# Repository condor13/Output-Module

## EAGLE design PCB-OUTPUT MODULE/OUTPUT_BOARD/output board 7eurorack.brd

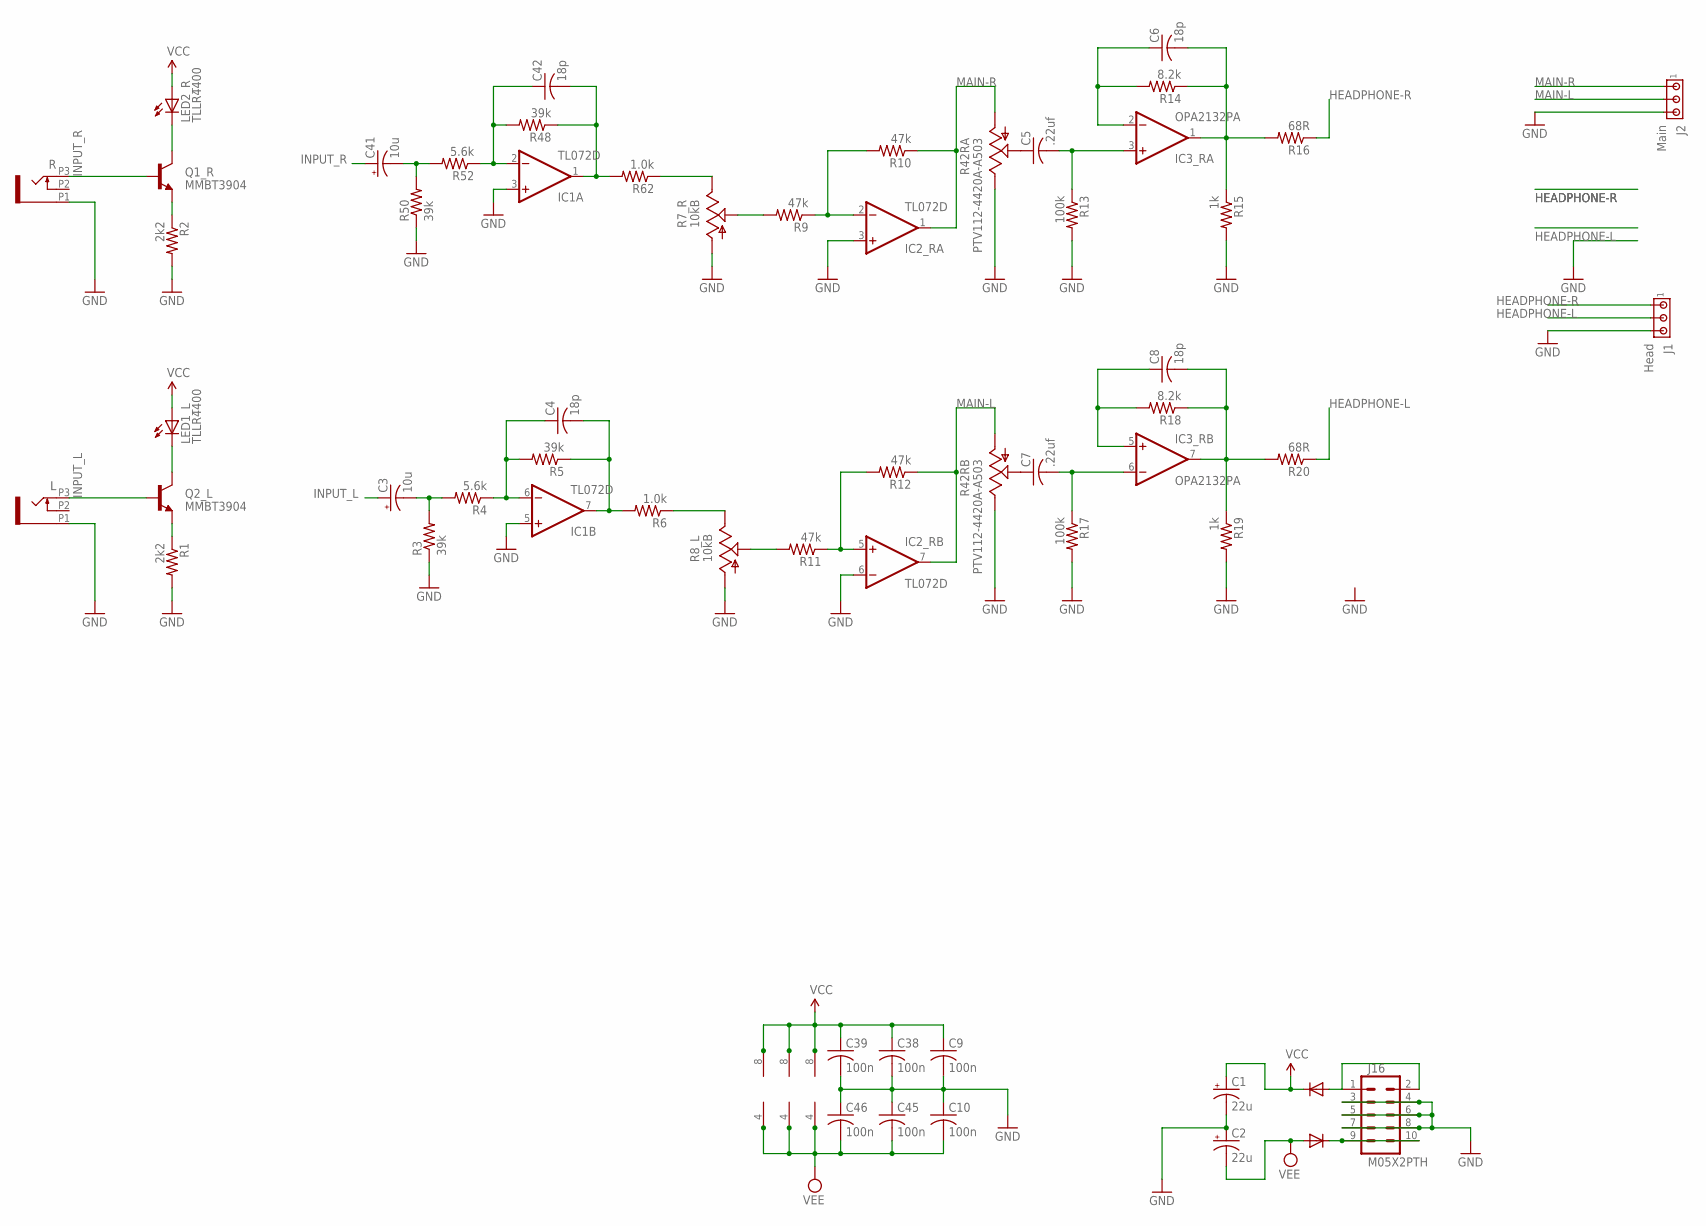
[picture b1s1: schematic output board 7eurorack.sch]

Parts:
C1, C2: 22u; PANASONIC_B
C3, C41: 10u; PANASONIC_B
C4, C6, C8, C42: 18p; C0603
C5, C7: .22uf; C0603
C9, C10, C38, C39, C45, C46: 100n; C0603
D1, D2: 1N5819HW; SOD123
IC1, IC2_R: TL072D; SO08
IC3_R: OPA2132PA; SO08
J1: Head; 10X03MTA
J2: Main; 10X03MTA
J16: M05X2PTH; AVR_ICSP
L: PJ301_THONKICONN6; WQP_PJ_301M6
LED1_L, LED2_R: TLLR4400; LED3MM
Q1_R, Q2_L: MMBT3904; SOT23-BEC
R: PJ301_THONKICONN6; WQP_PJ_301M6
R1, R2: 2k2; R0603
R3, R5, R48, R50: 39k; R0603
R4, R52: 5.6k; R0603
R6, R62: 1.0k; R0603
R7_R, R8_L: 10kB; ALPS_POT_VERTICAL_PS
R9, R10, R11, R12: 47k; R0603
R13, R17: 100k; R0603
R14, R18: 8.2k; R0603
R15, R19: 1k; R0603
R16, R20: 68R; R0603
R42: PTV112-4420A-A503; BOURNS_PTV112

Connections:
GND: C1.-, C2.+, C9.2, C10.1, C38.2, C39.2, C45.1, C46.1, IC1.3 (+IN), IC1.5 (+IN), IC2_R.3 (+IN), IC2_R.6 (-IN), J1.3, J2.3, J16.3, J16.4, J16.5, J16.6, J16.7, J16.8, L.P1 (1), R.P1 (1), R1.2, R2.2, R3.1, R7_R.P$3 (A), R8_L.P$3 (A), R13.2, R15.2, R17.2, R19.2, R42.3 (E), R42.3P (E), R50.1
HEADPHONE-L: J1.2, R20.1
HEADPHONE-R: J1.1, R16.1
INPUT_L: C3.+, L.P3 (3), Q2_L.B
INPUT_R: C41.+, Q1_R.B, R.P3 (3)
MAIN-L: IC2_R.7 (OUT), J2.2, R12.1, R42.1 (A)
MAIN-R: IC2_R.1 (OUT), J2.1, R10.1, R42.1P (A)
unnamed: D2.C, J16.9, J16.10
unnamed: Q2_L.E, R1.1
unnamed: Q1_R.E, R2.1
unnamed: C3.-, R3.2, R4.2
unnamed: C4.1, IC1.6 (-IN), R4.1, R5.2
unnamed: D1.A, J16.1, J16.2
unnamed: LED1_L.K (C), Q2_L.C
unnamed: LED2_R.K (C), Q1_R.C
unnamed: C4.2, IC1.7 (OUT), R5.1, R6.2
unnamed: R8_L.P$2 (S), R11.2
unnamed: R7_R.P$2 (S), R9.2
unnamed: IC2_R.2 (-IN), R9.1, R10.2
unnamed: IC2_R.5 (+IN), R11.1, R12.2
unnamed: C7.1, R42.2 (S)
unnamed: C5.2, IC3_R.3 (+IN), R13.1
unnamed: C6.2, IC3_R.1 (OUT), R14.1, R15.1, R16.2
unnamed: C6.1, IC3_R.2 (-IN), R14.2
unnamed: C7.2, IC3_R.6 (-IN), R17.1
unnamed: C8.2, IC3_R.7 (OUT), R18.1, R19.1, R20.2
unnamed: C41.-, R50.2, R52.2
unnamed: C8.1, IC3_R.5 (+IN), R18.2
unnamed: C42.1, IC1.2 (-IN), R48.2, R52.1
unnamed: C5.1, R42.2P (S)
unnamed: C42.2, IC1.1 (OUT), R48.1, R62.2
ROUT_JACK: R7_R.P$1 (E), R62.1
ROUT_JACK1: R6.1, R8_L.P$1 (E)
VCC: C1.+, C9.1, C38.1, C39.1, D1.C, IC1.8 (V+), IC2_R.8 (V+), IC3_R.8 (V+), LED1_L.A, LED2_R.A
VEE: C2.-, C10.2, C45.2, C46.2, D2.A, IC1.4 (V-), IC2_R.4 (V-), IC3_R.4 (V-)

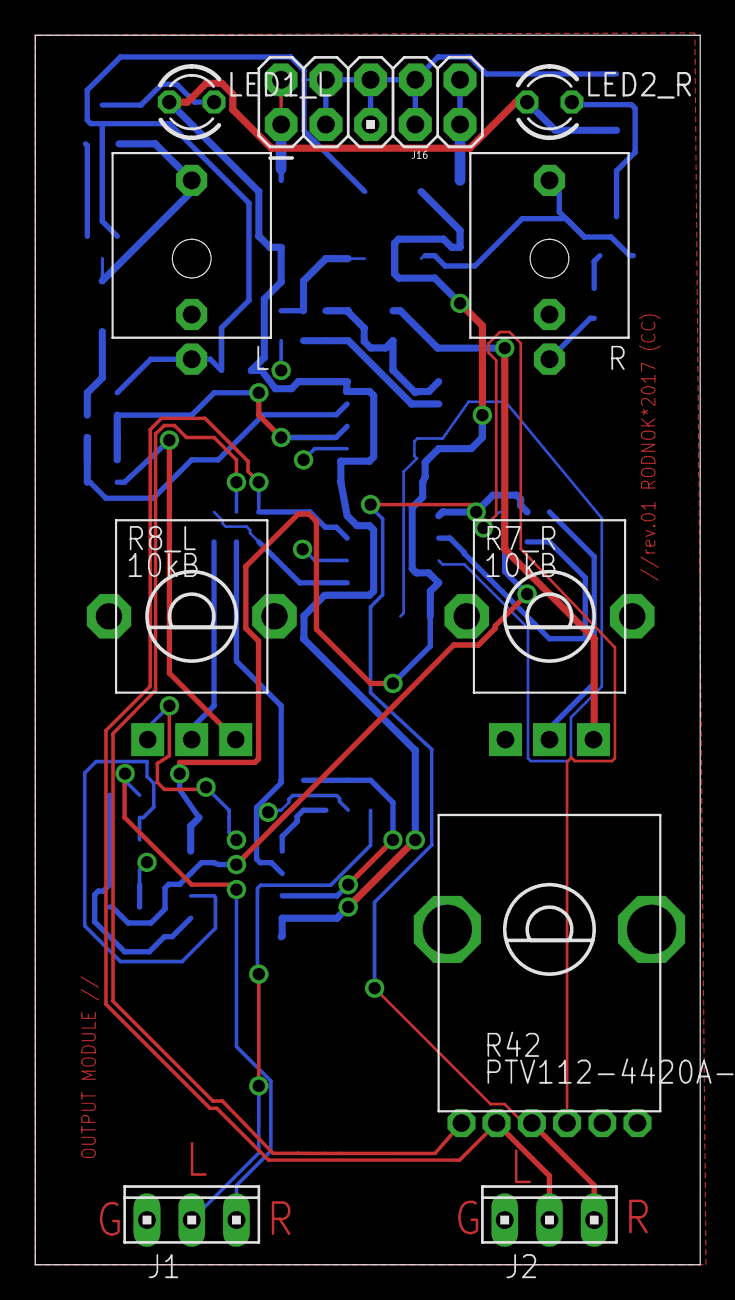
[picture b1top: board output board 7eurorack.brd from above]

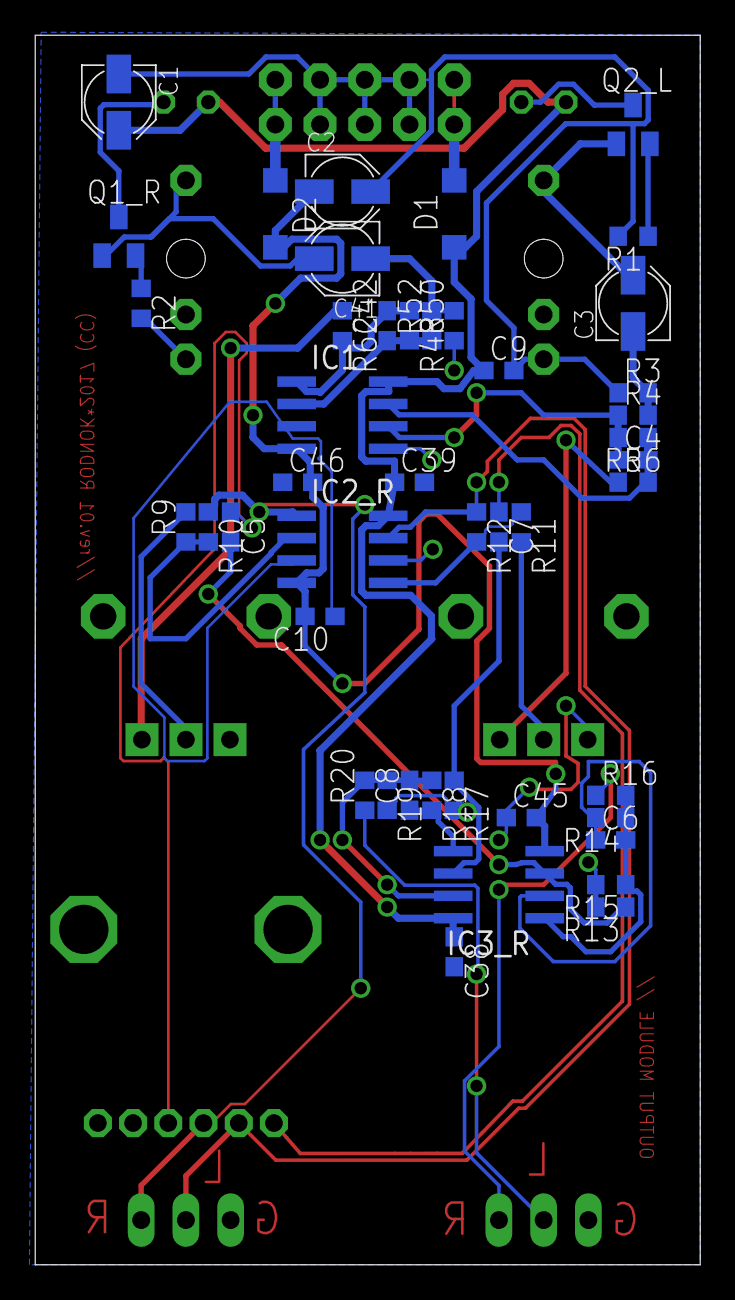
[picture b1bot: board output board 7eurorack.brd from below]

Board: 2 copper layers, 37.8 x 69.8 mm, 55 parts (45 on the bottom side), 35 nets.
